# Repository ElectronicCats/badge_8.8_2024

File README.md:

# Badge Addon 8.8 2024

## Tecnologia

- Puya
- LEDs
- Holder CR2032

## Gratitude
Do you want to say thank you? Tag these companies on social networks and show them your badge, thanks to them it is possible

- [ElectronicCats](https://electroniccats.com/)

## License

Electronic Cats invests time and resources providing this open source design, please support Electronic Cats and open-source hardware by purchasing products from Electronic Cats!

Designed by Electronic Cats.

Hardware released under an CERN Open Hardware Licence v1.2. See the LICENSE_HARDWARE file for more information.

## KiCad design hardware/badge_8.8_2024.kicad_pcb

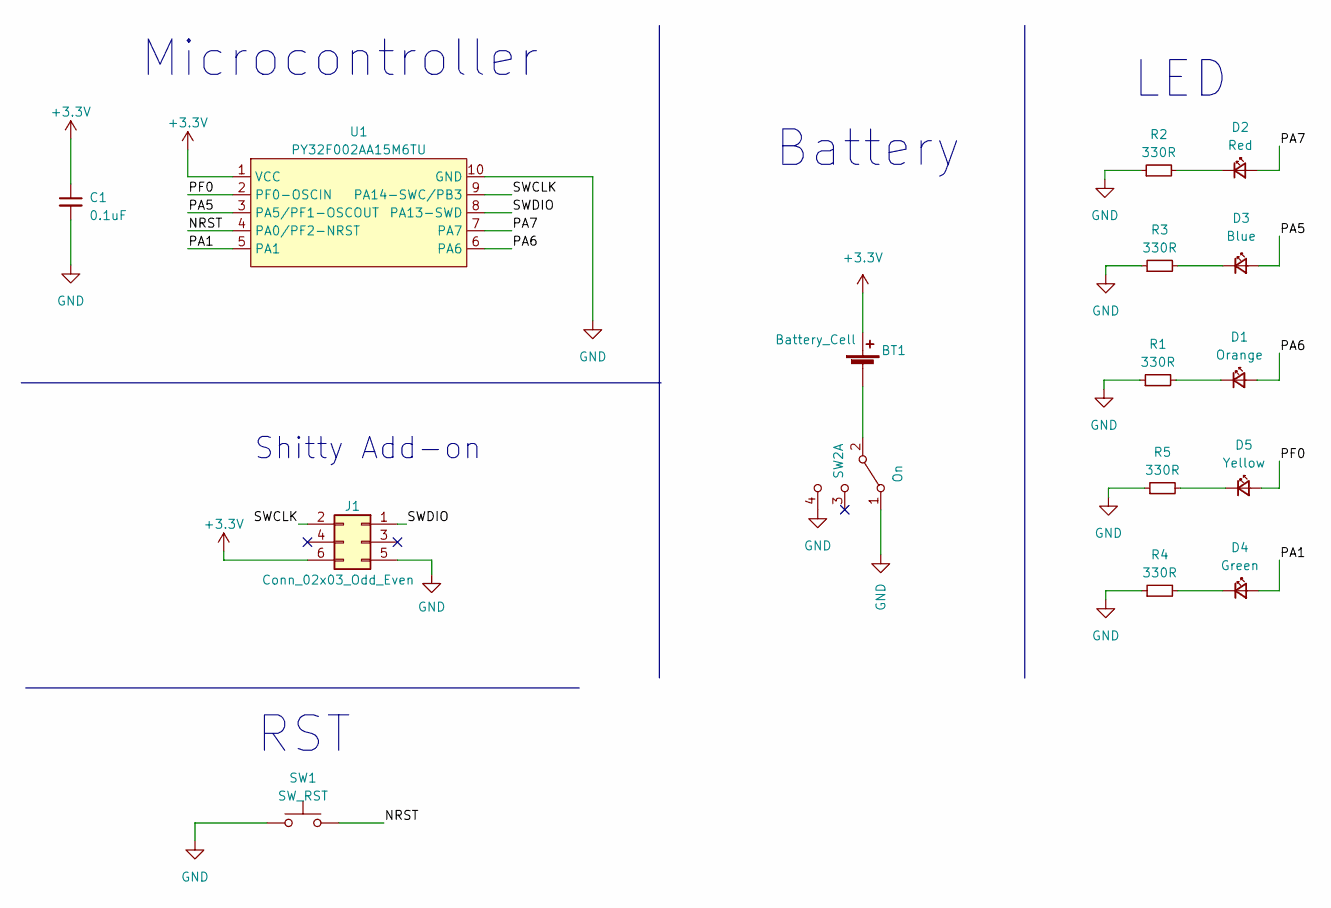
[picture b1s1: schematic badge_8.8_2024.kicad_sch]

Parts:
BT1: Battery_Cell; BAT-HLD-001; LCSC# C964833
C1: 0.1uF; C_0805_2012Metric; LCSC# C235731
D1: Orange; LED_0805_2012Metric; LCSC# C434437
D2: Red; LED_0805_2012Metric; LCSC# C965812
D3: Blue; LED_0805_2012Metric; LCSC# C205441
D4: Green; LED_0805_2012Metric; LCSC# C965815
D5: Yellow; LED_0805_2012Metric; LCSC# C84261
J1: Conn_02x03_Odd_Even; B-2100N06P-B111_CKM; LCSC# C124390
R1, R2, R3, R4, R5: 330R; R_0805_2012Metric; LCSC# C119075
SW1: SW_RST; SW_SPST_TL3342; LCSC# C318889
SW2: On; MSK12C02; LCSC# C431540
U1: PY32F002AA15M6TU; PY32F002AA15M; LCSC# C5292058

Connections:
+3.3V: BT1.2 (+), C1.1, J1.6, U1.1 (VCC)
/NRST: SW1.2, U1.4 (PA0/PF2-NRST)
/PA1: D4.2 (A), U1.5 (PA1)
/PA5: D3.2 (A), U1.3 (PA5/PF1-OSCOUT)
/PA6: D1.2 (A), U1.6 (PA6)
/PA7: D2.2 (A), U1.7 (PA7)
/PF0: D5.2 (A), U1.2 (PF0-OSCIN)
/SWCLK: J1.2, U1.9 (PA14-SWC/PB3)
/SWDIO: J1.1, U1.8 (PA13-SWD)
GND: C1.2, J1.5, R1.1, R2.1, R3.1, R4.1, R5.1, SW1.1, SW2.1 (A), SW2.4 (C), U1.10 (GND)
unnamed: BT1.1 (-), SW2.2 (B)
unnamed: D1.1 (K), R1.2
unnamed: D2.1 (K), R2.2
unnamed: D3.1 (K), R3.2
unnamed: D4.1 (K), R4.2
unnamed: D5.1 (K), R5.2

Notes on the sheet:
Microcontroller
Battery
Shitty Add-on
RST
LED

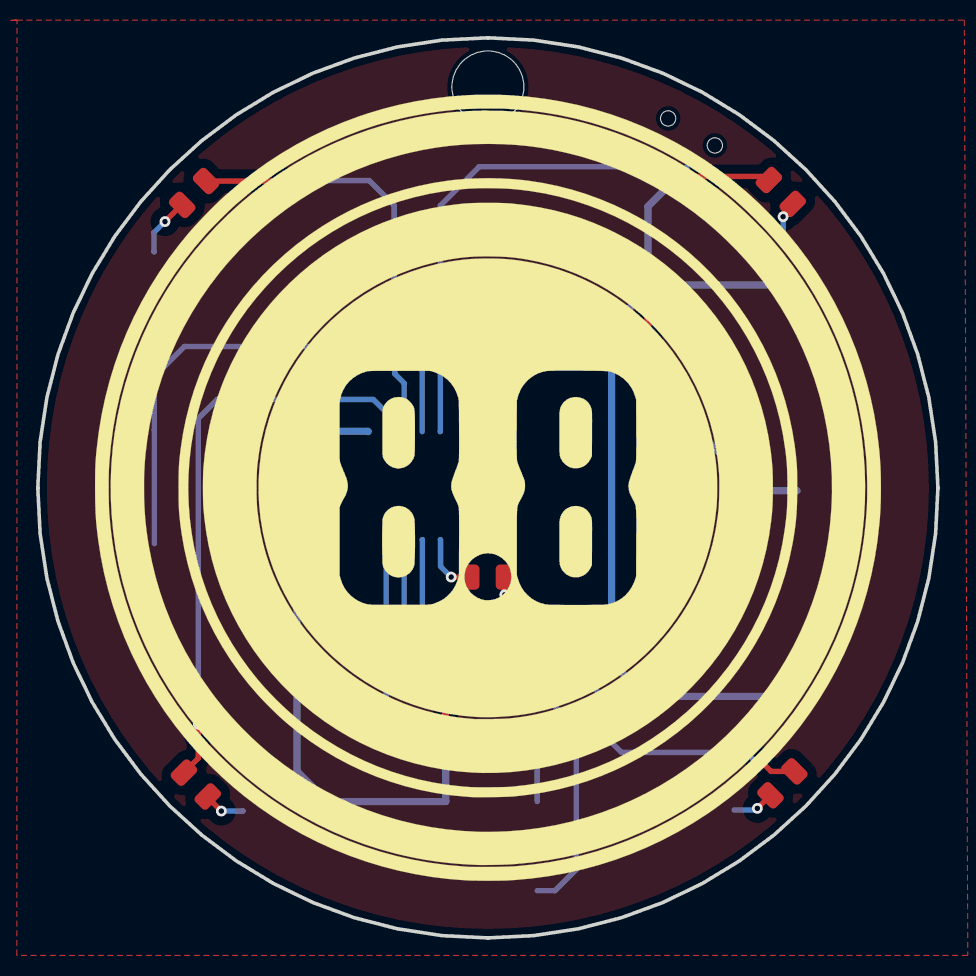
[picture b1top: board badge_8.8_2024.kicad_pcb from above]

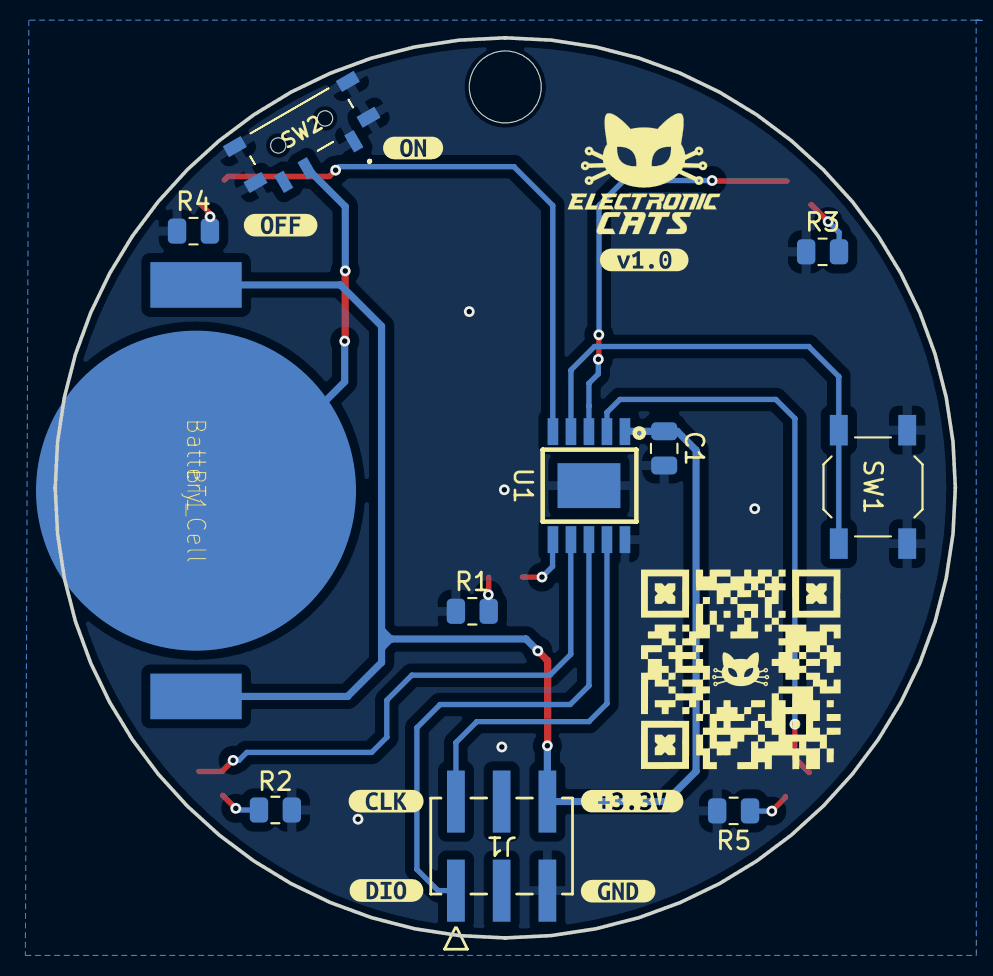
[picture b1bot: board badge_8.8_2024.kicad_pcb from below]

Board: 2 copper layers, 50.0 x 50.0 mm, 24 parts (18 on the bottom side), 16 nets.

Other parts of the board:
Ref**: Val**; BADGE 8.8 _Nuevo archivo
kibuzzard-66EC9C8E: G***; kibuzzard-66EC9C8E
kibuzzard-66EC9CA5: G***; kibuzzard-66EC9CA5
kibuzzard-66EC9D2A: G***; kibuzzard-66EC9D2A
kibuzzard-66EC9DE2: G***; kibuzzard-66EC9DE2
kibuzzard-66ECA9F9: G***; kibuzzard-66ECA9F9
kibuzzard-66ECAA39: G***; kibuzzard-66ECAA39
kibuzzard-66EDECB6: G***; kibuzzard-66EDECB6

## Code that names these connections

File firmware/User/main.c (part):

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
// Pin Definition 
uint32_t ports[] = {GPIOA, GPIOA, GPIOA, GPIOF, GPIOA};
uint8_t pins[] = {0x0020, 0x0002, 0x0080, 0x0001, 0x0040}; // PA5, PA1, PA7, PF0, PA6  - Each Badge have its own order. Indicator=PA6
uint8_t indicatorPos=4;

uint8_t message[] = {"8.8"};    //Secret Code
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// Sequence 1
void crossSequence()
{
  HAL_GPIO_OnPin(ports[0], pins[0]); // Start with PA5
  HAL_Delay(delay2);
  HAL_GPIO_OffPin(ports[0], pins[0]);
  HAL_GPIO_OnPin(ports[2], pins[2]);
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  HAL_GPIO_OffPin(ports[1], pins[1]);
  HAL_GPIO_OnPin(ports[3], pins[3]);
  HAL_Delay(delay2);
  HAL_GPIO_OffPin(ports[3], pins[3]); // Turn off PF0
  HAL_Delay(delay2);
}

void crossSequence2()
{
  HAL_GPIO_OnPin(ports[0], pins[0]); // Start with PF0
  HAL_GPIO_OnPin(ports[2], pins[2]); // Start with PA7
  HAL_Delay(delay2);
  HAL_GPIO_OffPin(ports[0], pins[0]);
  HAL_GPIO_OffPin(ports[2], pins[2]);
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
void followSequence()
{
  HAL_GPIO_OnPin(ports[0], pins[0]); // Start with PA5
  HAL_Delay(delay3);
  HAL_GPIO_OnPin(ports[1], pins[1]);
  HAL_GPIO_OnPin(ports[3], pins[3]);
  HAL_Delay(delay3);
  HAL_GPIO_OffPin(ports[0], pins[0]); // Turn off PA5
  HAL_GPIO_OnPin(ports[2], pins[2]);
  HAL_Delay(delay3);
  HAL_GPIO_OffPin(ports[1], pins[1]); // Turn off PA5
  HAL_GPIO_OffPin(ports[3], pins[3]);
  HAL_Delay(delay3);
  HAL_GPIO_OffPin(ports[2], pins[2]); // Turn off PA7
  HAL_Delay(delay3);
  //Reverse
  /*HAL_GPIO_OnPin(ports[2], pins[2]); // Start with PA7
  HAL_Delay(delay3);
  HAL_GPIO_OnPin(ports[1], pins[1]);
  HAL_GPIO_OnPin(ports[3], pins[3]);
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  HAL_GPIO_OffPin(ports[1], pins[1]); 
  HAL_GPIO_OffPin(ports[3], pins[3]);
  HAL_Delay(delay3);
  HAL_GPIO_OffPin(ports[0], pins[0]); // Turn off PA5
  HAL_Delay(delay2);*/
}

void fastFlash()
{
  HAL_GPIO_OnPin(ports[0], pins[0]); // Start with PA5
  HAL_Delay(delay);
  HAL_GPIO_OnPin(ports[1], pins[1]);
  HAL_GPIO_OnPin(ports[3], pins[3]);
  HAL_Delay(delay);
  HAL_GPIO_OffPin(ports[0], pins[0]); // Turn off PA5
  HAL_GPIO_OnPin(ports[2], pins[2]);
  HAL_Delay(delay);
  HAL_GPIO_OffPin(ports[1], pins[1]); // Turn off PA5
  HAL_GPIO_OffPin(ports[3], pins[3]);
  HAL_Delay(delay);
  HAL_GPIO_OffPin(ports[2], pins[2]); // Turn off PA7
  HAL_Delay(delay);
}
/*
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
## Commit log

2024-09-19 feat(Hw):Init_Schematic_And_PCB
2024-09-19 feat(Hw):Update_PCB
2024-09-20 feat(Hw):Add_label
2024-09-20 feat(Hw):Add_labels
2024-09-20 feat(Hw):Update_Labeles
2024-09-20 feat(Hw):Update_Lables
2024-10-03 chore: update gitignore
2024-10-03 feat (fw): init code
2024-10-03 feat(fw): update sequences to circular pattern
2024-10-03 feat (fw): update sequences and fix secret code
2024-10-24 docs: Update README.md
2025-01-29 feat: Create LICENSE_HARDWARE.md

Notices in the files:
firmware/User/main.c:
© Copyright (c) Puya Semiconductor Co.
All rights reserved.
© Copyright (c) 2016 STMicroelectronics.
This software component is licensed by ST under BSD 3-Clause license,
the "License"; You may not use this file except in compliance with the
License. You may obtain a copy of the License at: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
(C) COPYRIGHT Puya *****END OF FILE
